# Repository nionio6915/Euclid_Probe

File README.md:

# EUCLID PROBE

The highly accurate, magneticaly coupled Z-Probe that is not affected by bed temp, bed material, magnetism or surface treatment.   

The probe can be configured to be used as Z-endstop, be manually or automatically deployed via gcode macros, and can take advantage of the firmware's probe pickup detection scheme to ensure pickup/release. It uses screw attached magnets for both mechanical coupling and for electrical contact. The Z-Probe circuit is completed when the probe is attached. 

The unique dock design securely captures the probe, providing secure and reliable docking and undocking. 

# We have moved all documentation to https://www.euclidprobe.com  
# All data and source files will remain here and be linked from here 

YouTube Channel - https://www.youtube.com/channel/UCIUXRiUfHCOrqRxitcH9O6g

Discussion and support is available as a subgroup to the CroXY Discord- https://discord.gg/jfnVrUx2uK   

Parts kits and fully assembled probes are available for purchase at www.euclidprobe.com. 

The most current info, including printable dock and mount files are also hosted at www.euclidprobe.com.

**<br />This work is licensed under a <a rel="license" href="http://creativecommons.org/licenses/by-nc-sa/4.0/">Creative Commons Attribution-NonCommercial-ShareAlike 4.0 International License</a>.**

## Euclid Probe YouTube Channel 

<a href="https://www.youtube.com/channel/UCIUXRiUfHCOrqRxitcH9O6g" target="new"><br>Euclid Probe YouTube channel</br></a>

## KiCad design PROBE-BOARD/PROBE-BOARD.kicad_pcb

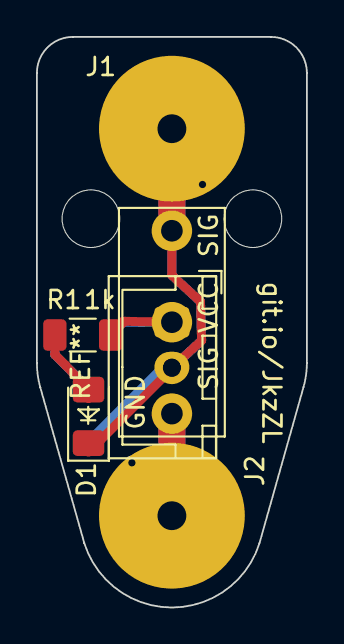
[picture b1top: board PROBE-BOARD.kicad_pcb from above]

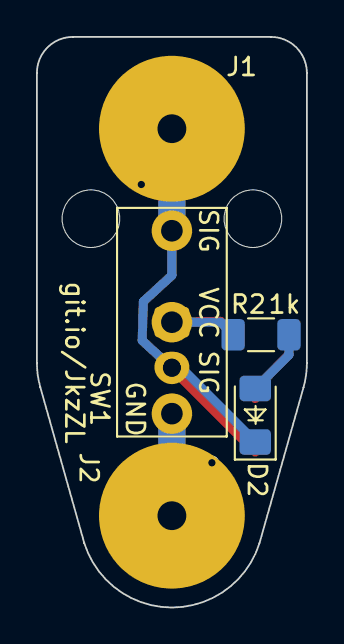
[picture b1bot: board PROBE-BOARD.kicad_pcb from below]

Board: 2 copper layers, 15.0 x 31.7 mm, 7 parts (2 on the bottom side), 5 nets.

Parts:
D1, D2: LED_Small; LED_1206_3216Metric_Pad1.42x1.75mm_HandSolder
J1, J2: Conn_01x01; MagPad
R1, R2: 1k; R_1206_3216Metric_Pad1.30x1.75mm_HandSolder
SW1: SW_Push_Open; D2F

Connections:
GND: J2.1, SW1.1
unnamed: D1.2, R1.2
unnamed: D2.2, R2.2
SIGNAL: D1.1, D2.1, J1.1, SW1.2, SW1.4
VCC: R1.1, R2.1, SW1.3

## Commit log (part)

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2021-06-05 Update README.md
    Updated image references
2021-06-05 Update README.md
    Updated Silks
2021-06-21 Added Dock info
2021-06-22 Added stls for mounts and adapters
2021-06-24 corrected isobtm image
2021-06-26 added polarity symbols
2021-07-05 Added Voron Afterburner #4 User mod
    Added Voron Afterburner #4 User mod as recessed Euclid Probe Mount
2021-07-16 Dock Updates
    Revised RailCore Docks and Mounts
2021-07-21 Updated PIP supports
2021-07-21 Dock Updates
2021-07-23 Macros added
2021-07-23 Create Example_deployprobeManual.g
    Added Manual Probe Deployment macro
2021-07-26 Voron 2.4 Bed Mount rev2
2021-08-17 updated stls
2021-09-04 updated docks
2021-09-14 added mounts
2021-09-24 Revised Voron parts
2021-09-25 Revised Probe Models
2021-09-27 Updated stls for Ender3, Ender5 and Voron
2021-09-30 Updated docks & Mounts
    Updated Ende3, Ender5, Omron/Fotek, Voron AfterBurner
2021-10-04 Rename Marlin_2.0_Config_notes.txt to readme.md
2021-10-28 updated cad of boards
2021-11-19 corrected typos in RRF3 files
2021-11-21 Corrected RRF2 macro example
2021-12-06 Files Reorganized
2021-12-08 Updated Klipper Macros
2021-12-08 updated stls, klipper macros
2021-12-10 Updated Qidi
2021-12-11 klipper config examples ad
2021-12-11 klipper updates
2021-12-11 fixed M5 length on Trident Dock
2021-12-11 File reorder
2021-12-11 updated Voron readme.md
2021-12-11 grammer-spelling
2021-12-11 md edits
2021-12-12 revised OmronMount
2021-12-12 image updates
2021-12-12 gantry mount V2
2021-12-12 typos
2021-12-12 fixed print orientation
2021-12-18 klipper macro updates
2021-12-22 Flie Cleanup
2021-12-25 VCore updates
2021-12-27 Updated V-Core files
2021-12-30 EVA Updates
2021-12-30 revised bore for screw
2022-01-02 updated EVA files
2022-01-05 MRWMount Update
2022-01-05 RC CAD files
2022-01-06 Solder Jigs revised
2022-01-09 RailCore updates
2022-01-09 Dimensioned Pictures
2022-01-09 Cleaned up triangles
2022-01-15 updated soldering jigs, added dxf versions
2022-01-20 Added pics to Voron folder
2022-01-21 Broke apart Gantry mount into 2 stls
2022-01-22 Added MGN12 Native Mount, Renamed to Clockwork1 for Voron Dev consistency
2022-01-22 Updated Voron CW1 files
2022-01-22 RRF Typo fix
2022-01-23 Added bedmap to RRF3 deploy macro
2022-01-23 added ascii graphics to RRF files
2022-01-25 V-Core Legacy Dock updated
2022-01-26 Klipper example revised to V3
2022-01-26 Hyprecube BLT Adapter Added
2022-01-30 Modular Parts Update
2022-02-07 updated solder jig
2022-02-07 confirm blocks up to date
2022-02-09 fixed RRF typo
2022-02-14 fixed typos rrf macro
2022-02-17 updated CW1 models
2022-02-17 updated voron parts
2022-02-22 voron stp files, klipper cfgs
2022-02-27 fixed typos in QGL
2022-02-27 added trident photos
2022-02-28 cleanup
2022-03-04 updates VCore EVA Mount
2022-03-06 Voron Bed Mount Updated
2022-03-06 Updated stp's
2022-03-06 Added Omron Mount Adapter Files to Voron folder
2022-03-16 VoronGantryMountV2
2022-03-18 fixed klipper configs
2022-03-19 mount tweaks
2022-03-21 fixed boltholes on Voron
2022-03-24 Ender3 Fixes
2022-03-29 cleaning up voron files
2022-03-30 Added mirrored V1 Gantry & Shorty Gantry
2022-04-05 replaced Ender folder
2022-04-08 RC jigs, Voron Gantry
2022-04-10 Voron Gantry Docks
2022-04-13 cleaned up marlin files
2022-04-20 updates to user_contrib files,stls, stp;s
2022-04-20 updated V4 cfg example to include start_print info
2022-04-21 commented out probe config and added notes
2022-04-21 moved gcode statement for debug
2022-04-30 added N-S to solder jigs
2022-04-30 Added N-S markings
2022-04-30 regenerated stp's
2022-04-30 typos and clarifications
2022-04-30 rebase
2022-05-02 zips
2022-05-13 fix open surface stps
2022-06-05 tweaked solder jigs, typos in V4 macros
2022-06-08 updated rrf moving dock and klipper V4
2022-06-12 VoronExpDock
2022-06-17 macro corrections
2022-06-21 klipper variable tweakes
2022-06-27 broke apart voron all parts to stps
2022-06-29 voron bed docks
2022-07-01 RRF3 Typo Correction Moving z Dock
2022-07-02 klipper variable type fixed
2022-07-05 No short cover that protect the probe when docked
    Only the two magnests are visible and a bit more sunk than cover
2022-07-11 UserMods
2022-07-11 User Contribs
2022-07-19 Add some images and readme
    Remove some data
2022-07-24 Fixing first_layer_*_xy variables to actually work
2022-07-25 Clean and simplify example Klipper config
    This is still based on my personal config, but with the more advanced
    stuff removed. If users want that stuff, they need to take the
    responsibility of configuring it themselves.
2022-07-27 example V5
2022-08-15 revised Z move after probe
    revised Z move after probe to bed clearance to clear probe from bed
2022-08-18 Added CW2_MGN12 parts for M2.5 mount
    I'm moving over to CW2 and use the native euclid mount. Chopped off the bottom of the CW1 version and put it on the bottom of the new CW2 RC1 piece that mounts to the front instead of through the bac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
2022-08-22 added m401/m402 notation
2022-09-27 CW2 updates
2022-10-25 Updated CW2 files, Omron Files
    Updated CW2 files, Omron Files
2022-11-03 corrected V3 typos
2022-11-09 Small fixes to Voron readme
2022-11-09 corrected klipper example
2023-02-16 Custom VZbot VZ-Printhead mount
    I've created a custom mount for the Euclid Probe for the VZ-Printhead. (Euclid mount VZ-printhead v5)
    It needs to be assembled onto the 5015 fan at the back.
    The dock that I used is the VoronGantyMountRev_4 filed down a little bit along with the RailCoreTopMountLong, assembled the other way to make the Mount fit.
    The image should make the assembly clearer.
    I've added the docks from the other repos here to make it easier to find the full assembly.
2023-02-16 edited readme
2023-02-20 spreadsheet motion plotter
2023-03-03 Excel Plotter, Updated Qidi Prts
    Excel Plotter, Updated Qidi Prts
2023-03-29 Added copies of drill jig to railcore
2023-03-30 bump dock updates
2023-04-02 Added gitignore for DS_Store files
2023-08-14 checked railcore files, renamed as checked
2023-11-06 typos in klipper v3 config
    typos in klipper v3 config
